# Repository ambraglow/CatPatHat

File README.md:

# CatPatHat

An addon for the Blepis, that lets you have a little PCB cat you can pet.

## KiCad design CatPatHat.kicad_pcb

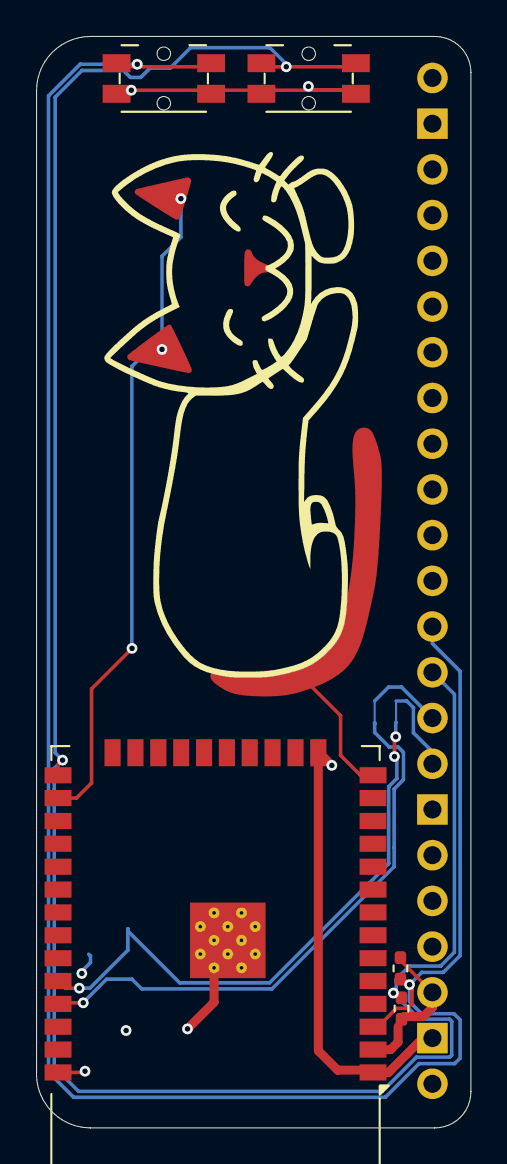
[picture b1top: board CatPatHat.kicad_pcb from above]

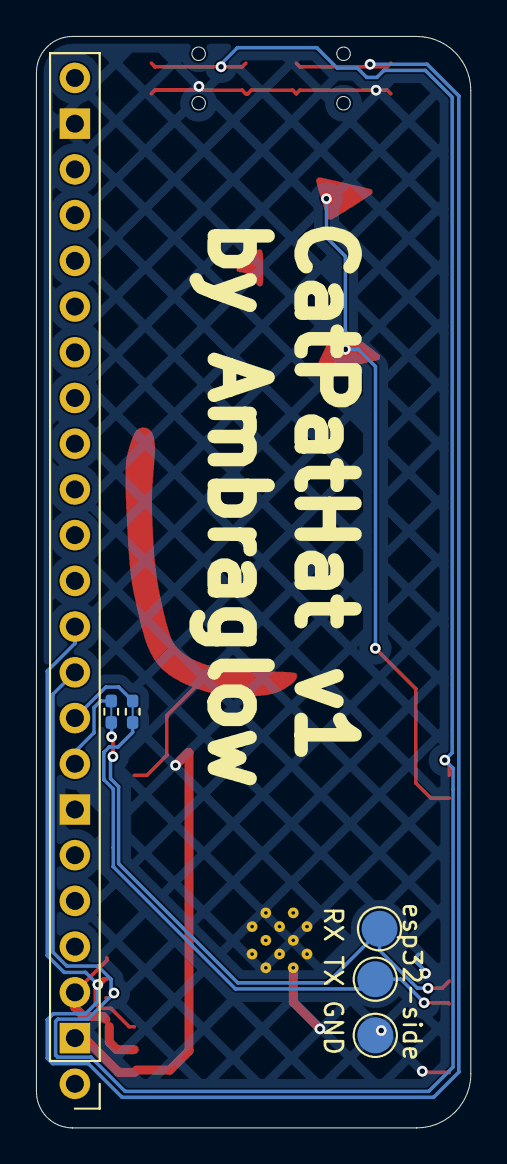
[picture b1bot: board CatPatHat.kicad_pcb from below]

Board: 2 copper layers, 24.1 x 60.6 mm, 13 parts (6 on the bottom side), 8 nets.

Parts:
J53: EXP; PinHeader_1x23_P2.54mm_Vertical
R1, R2, R3, R4: 0; R_0402_1005Metric_Pad0.72x0.64mm_HandSolder
SW1, SW2: SW_Push; Panasonic_EVQPUL_EVQPUC
TP1, TP2, TP3: TestPoint; TestPoint_Pad_D2.0mm
TP4: TestPoint; cat_tail
TP5: TestPoint; catears
U3: ESP32-WROOM-32

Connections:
+3V3PI_p: J53.3, R3.2, R4.2, U3.2 (VDD)
/BOOT: J53.10, R3.1, SW2.1, U3.25 (IO0)
/Pi_GPIO14_p: J53.8, R2.1
/Pi_GPIO15_p: J53.9, R1.2
/Pi_GPIO17: J53.11, R4.1, SW1.1, U3.3 (EN)
GND: J53.2, J53.7, J53.22, SW1.2, SW2.2, TP3.1 (1_1), U3.1 (GND), U3.15 (GND), U3.38 (GND), U3.39 (GND)
unnamed: R2.2, TP1.1 (1_1), U3.34 (RXD0/IO3)
unnamed: R1.1, TP2.1 (1_1), U3.35 (TXD0/IO1)
